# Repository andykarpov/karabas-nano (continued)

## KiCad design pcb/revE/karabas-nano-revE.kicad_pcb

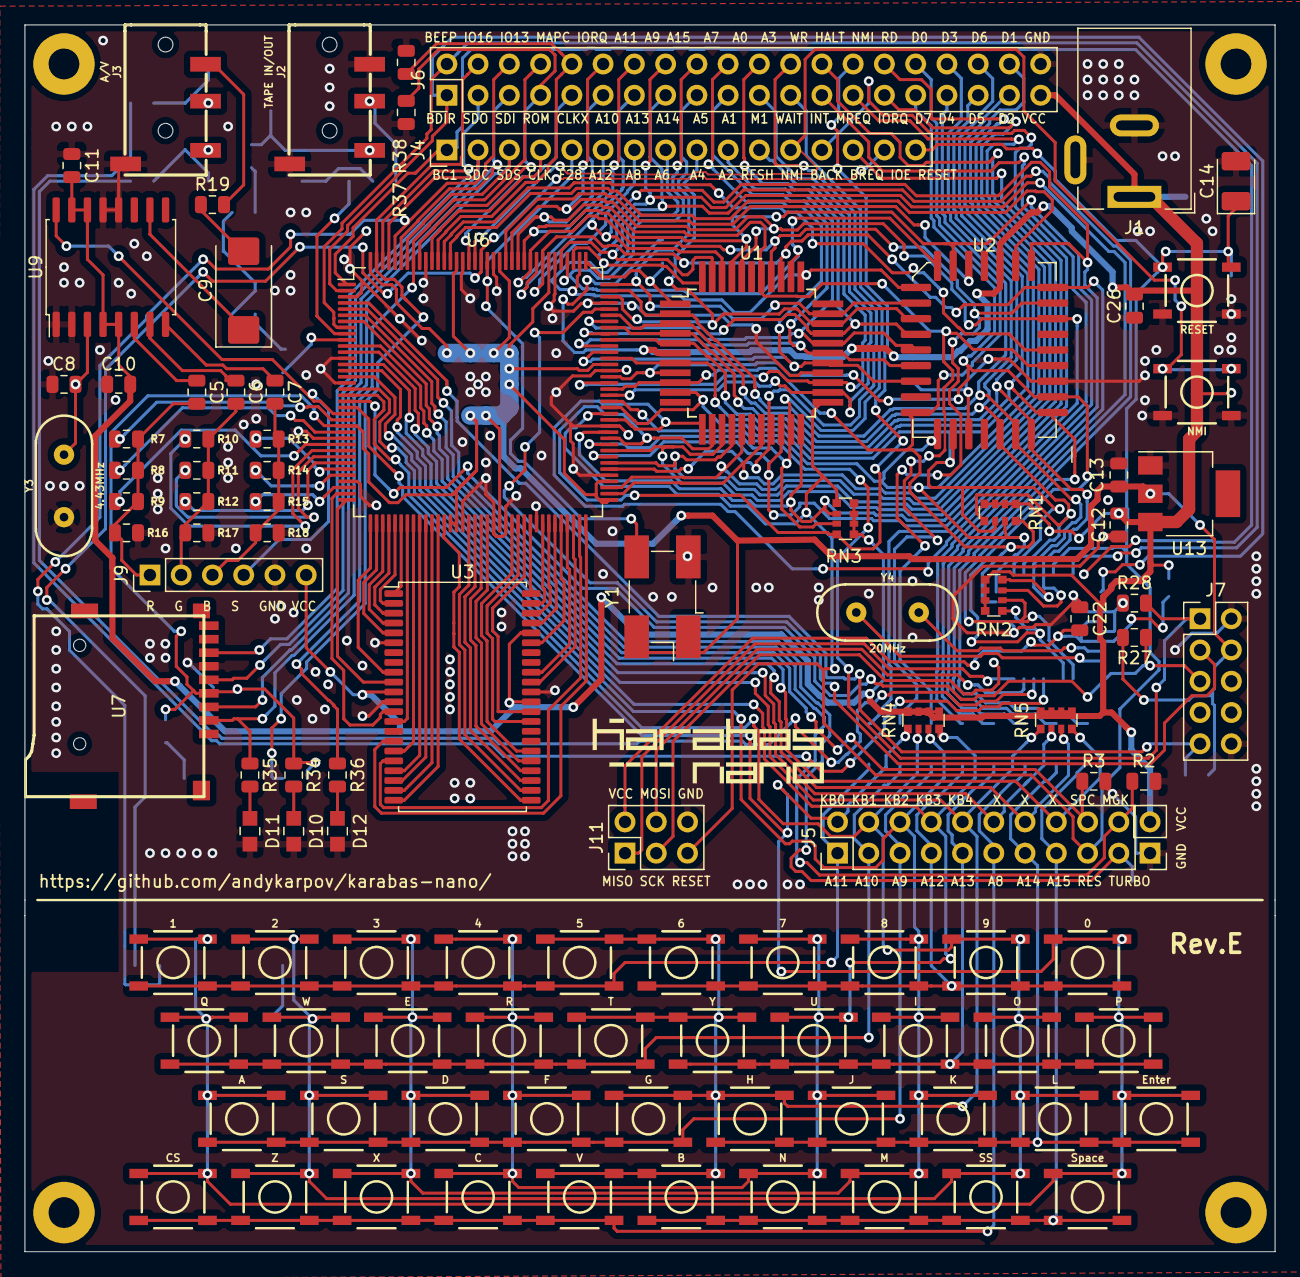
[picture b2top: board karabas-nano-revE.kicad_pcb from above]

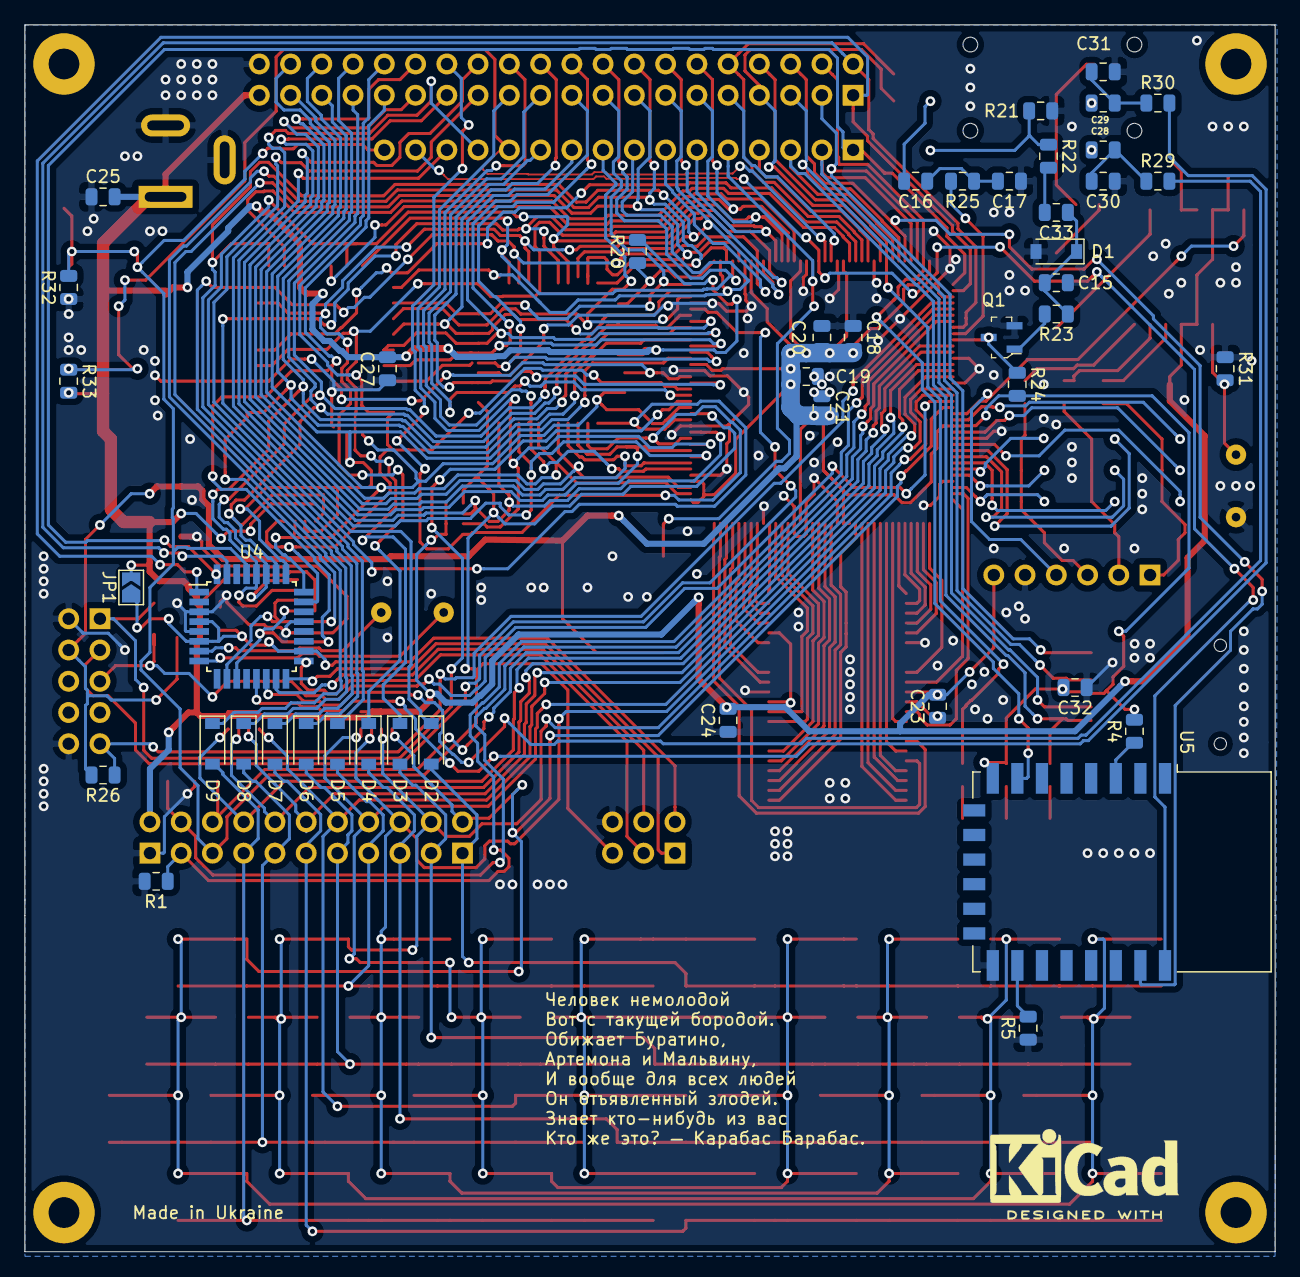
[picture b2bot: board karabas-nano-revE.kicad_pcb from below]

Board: 2 copper layers, 101.6 x 99.7 mm, 153 parts (45 on the bottom side), 160 nets.

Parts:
C5, C6, C7, C16, C18, C19, C20, C21, C22, C23, C24, C25, C26, C27, C32: 100nF; C_0805_2012Metric
C8: 10p; C_0805_2012Metric
C9: 220uF; CP_EIA-7343-31_Kemet-D_Pad2.25x2.55mm_HandSolder
C10, C11, C12, C13, C28, C29: 10uF; C_0805_2012Metric
C14: 10uF; CP_EIA-3528-21_Kemet-B_Pad1.50x2.35mm_HandSolder
C15, C33: 10nF; C_0805_2012Metric
C17: 3n3; C_0805_2012Metric
C30, C31: 1nF; C_0805_2012Metric
D1, D2, D3, D4, D5, D6, D7, D8, D9: 1N4148W; D_SOD-123
D10: PWR; 0805
D11: SD; 0805
D12: MMC; 0805
H1, H2, H3, H4: MountingHole; MountingHole_2.5mm_Pad
J1: DC 5V; BarrelJack_Wuerth_6941xx301002
J2: TAPE IN/OUT; AUDIO_JACK_3.5MM_SMD
J3: A/V; AUDIO_JACK_3.5MM_SMD
J4: BUS; PinHeader_1x16_P2.54mm_Vertical
J5: KEYBOARD; PinHeader_2x10_P2.54mm_Vertical
J6: BUS; PinHeader_2x20_P2.54mm_Vertical
J7: JTAG; PinHeader_2x05_P2.54mm_Vertical
J9: RGB; PinHeader_1x06_P2.54mm_Vertical
J10: PWR; PinHeader_1x02_P2.54mm_Vertical
J11: AVR ISP; PinHeader_2x03_P2.54mm_Vertical
JP1: SolderJumper_2_Open; SolderJumper-2_P1.3mm_Open_TrianglePad1.0x1.5mm
Q1: BC846B; SOT-23-3
R1, R2, R3, R4, R5, R21, R23, R24, R26, R27, R28, R29, R30, R33, R37, R38: 10k; R_0805_2012Metric
R7, R10, R13, R22: 510; R_0805_2012Metric
R8, R11, R14: 1k; R_0805_2012Metric
R9, R12, R15: 2k; R_0805_2012Metric
R16, R17, R18, R19: 75; R_0805_2012Metric
R20: 2k2; R_0805_2012Metric
R25: 33k; R_0805_2012Metric
R31: 4,7M; R_0805_2012Metric
R32: 47k; R_0805_2012Metric
R34, R35, R36: 470; R_0805_2012Metric
RN1, RN2, RN3, RN4, RN5: 10k; R_Array_Convex_4x0612
SW1: RESET; TACTILE_SWITCH_SMD_5.2MM
SW2: NMI; TACTILE_SWITCH_SMD_5.2MM
SW3: 1; TACTILE_SWITCH_SMD_5.2MM
SW4: 2; TACTILE_SWITCH_SMD_5.2MM
SW5: 3; TACTILE_SWITCH_SMD_5.2MM
SW6: 4; TACTILE_SWITCH_SMD_5.2MM
SW7: 5; TACTILE_SWITCH_SMD_5.2MM
SW8: 6; TACTILE_SWITCH_SMD_5.2MM
SW9: 7; TACTILE_SWITCH_SMD_5.2MM
SW10: 8; TACTILE_SWITCH_SMD_5.2MM
SW11: 9; TACTILE_SWITCH_SMD_5.2MM
SW12: 0; TACTILE_SWITCH_SMD_5.2MM
SW13: Q; TACTILE_SWITCH_SMD_5.2MM
SW14: A; TACTILE_SWITCH_SMD_5.2MM
SW15: CS; TACTILE_SWITCH_SMD_5.2MM
SW16: W; TACTILE_SWITCH_SMD_5.2MM
SW17: S; TACTILE_SWITCH_SMD_5.2MM
SW18: Z; TACTILE_SWITCH_SMD_5.2MM
SW19: E; TACTILE_SWITCH_SMD_5.2MM
SW20: D; TACTILE_SWITCH_SMD_5.2MM
SW21: X; TACTILE_SWITCH_SMD_5.2MM
SW22: R; TACTILE_SWITCH_SMD_5.2MM
SW23: F; TACTILE_SWITCH_SMD_5.2MM
SW24: C; TACTILE_SWITCH_SMD_5.2MM
SW25: T; TACTILE_SWITCH_SMD_5.2MM
SW26: G; TACTILE_SWITCH_SMD_5.2MM
SW27: V; TACTILE_SWITCH_SMD_5.2MM
SW28: Y; TACTILE_SWITCH_SMD_5.2MM
SW29: H; TACTILE_SWITCH_SMD_5.2MM
SW30: B; TACTILE_SWITCH_SMD_5.2MM
SW31: U; TACTILE_SWITCH_SMD_5.2MM
SW32: J; TACTILE_SWITCH_SMD_5.2MM
SW33: N; TACTILE_SWITCH_SMD_5.2MM
SW34: I; TACTILE_SWITCH_SMD_5.2MM
SW35: K; TACTILE_SWITCH_SMD_5.2MM
SW36: M; TACTILE_SWITCH_SMD_5.2MM
SW37: O; TACTILE_SWITCH_SMD_5.2MM
SW38: L; TACTILE_SWITCH_SMD_5.2MM
SW39: SS; TACTILE_SWITCH_SMD_5.2MM
SW40: P; TACTILE_SWITCH_SMD_5.2MM
SW41: Enter; TACTILE_SWITCH_SMD_5.2MM
SW42: Space; TACTILE_SWITCH_SMD_5.2MM
U1: Z80; TQFP-44_14x14mm_P0.8mm
U2: 27C512; PLCC-32_11.4x14.0mm_P1.27mm-bigpads
U3: BS62LV1600; TSOP-II-44_10.16x18.41mm_P0.8mm
U4: ATmega8A-AU; TQFP-32_7x7mm_P0.8mm
U5: ESP-12E
U6: EPM3256ATC144; LQFP-144_20x20mm_P0.5mm
U7: MicroSD; GCT-MEM2055-00-190-01-A
U9: AD724; SOIC-16W_7.5x10.3mm_P1.27mm
U13: LM1117-3.3; SOT-223
Y1: 28MHz; Oscillator_SMD_EuroQuartz_XO91-4Pin_7.0x5.0mm_HandSoldering
Y3: 4.43MHz; HC49US
Y4: 20MHz; HC49US

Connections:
+3V3: C13.2, C18.2, C19.2, C20.2, C21.2, C32.2, J7.4, R4.2, R24.2, R26.2, R27.2, R34.1, U5.8, U6.24, U6.50, U6.51, U6.58, U6.73, U6.76, U6.95, U6.115, U6.123, U6.130, U6.144, U7.4, U13.2, Y1.1, Y1.4
/A0: J6.20, U1.27, U2.11, U6.97
/A1: J6.19, U1.28, U2.10, U6.98
/A2: J4.10, U1.29, U2.9, U6.100
/A3: J6.22, U1.30, U2.8, U6.102
/A4: J4.9, U1.31, U2.7, U6.106
/A5: J6.17, U1.32, U2.6, U6.108
/A6: J4.8, U1.34, U2.5, U6.110
/A7: J6.18, U1.35, U2.4, U6.112
/A8: D7.1, J4.7, U1.36, U2.29, U6.116
/A9: D4.1, J6.14, U1.37, U2.28, U6.118
/A10: D3.1, J6.11, U1.38, U2.24, U6.120
/A11: D2.1, J6.12, U1.40, U2.27, U6.121
/A12: D5.1, J4.6, U1.41, U2.3, U6.119
/A13: D6.1, J6.13, U1.42, U2.30, U6.117
/A14: D8.1, J6.15, U1.43, U6.113
/A15: D9.1, J6.16, U1.44, U6.111
/AVR_MISO: J11.1, U4.16
/AVR_MOSI: J11.4, U4.15
/AVR_SCK: J11.3, U4.17
/AY_BC1: J4.1, U4.32, U6.1
/AY_BDIR: J6.1, U4.1, U6.2
/AY_OUT_L: R30.2, U4.13
/AY_OUT_R: R29.2, U4.14
/B0: R15.1, U6.34
/B1: R14.1, U6.32
/B2: R13.1, U6.31
/BEEPER: J6.2, U4.31, U6.8
/BLUE: C7.2, J9.3, R13.2, R14.2, R15.2, R18.1
/CLK28: J4.5, U6.125, Y1.3
/CLKX: J6.9, U6.128
/CLK_BUS: J4.4, U6.134
/CLK_CPU: R20.1, U1.1, U6.109
/CSYNC: J9.4, U6.22, U9.16
/D0: J6.32, RN1.4, U1.9, U2.13, U4.23, U6.91
/D1: J6.38, RN1.3, U1.10, U2.14, U4.24, U6.88
/D2: J6.37, RN1.2, U1.7, U2.15, U4.25, U6.96
/D3: J6.34, RN1.1, U1.3, U2.18, U4.26, U6.103
/D4: J6.33, RN2.4, U1.2, U2.19, U4.27, U6.107
/D5: J6.35, RN2.3, U1.4, U2.20, U4.28, U6.101
/D6: J6.36, RN2.2, U1.5, U2.21, U4.10, U6.99
/D7: J6.31, RN2.1, U1.8, U2.22, U4.11, U6.93
/G0: R12.1, U6.30
/G1: R11.1, U6.29
/G2: R10.1, U6.28
/GREEN: C6.2, J9.2, R10.2, R11.2, R12.2, R17.1
/IO13: J6.6, U5.21, U6.140
/IO16: J6.4, U5.7, U6.143
/IOE: J4.15, U5.22, U6.126
/KA8: D7.2, J5.11, SW15.1, SW15.2, SW18.1, SW18.2, SW21.1, SW21.2, SW24.1, SW24.2, SW27.1, SW27.2
/KA9: D4.2, J5.5, SW14.1, SW14.2, SW17.1, SW17.2, SW20.1, SW20.2, SW23.1, SW23.2, SW26.1, SW26.2
/KA10: D3.2, J5.3, SW13.1, SW13.2, SW16.1, SW16.2, SW19.1, SW19.2, SW22.1, SW22.2, SW25.1, SW25.2
/KA11: D2.2, J5.1, SW3.1, SW3.2, SW4.1, SW4.2, SW5.1, SW5.2, SW6.1, SW6.2, SW7.1, SW7.2
/KA12: D5.2, J5.7, SW8.1, SW8.2, SW9.1, SW9.2, SW10.1, SW10.2, SW11.1, SW11.2, SW12.1, SW12.2
/KA13: D6.2, J5.9, SW28.1, SW28.2, SW31.1, SW31.2, SW34.1, SW34.2, SW37.1, SW37.2, SW40.1, SW40.2
/KA14: D8.2, J5.13, SW29.1, SW29.2, SW32.1, SW32.2, SW35.1, SW35.2, SW38.1, SW38.2, SW41.1, SW41.2
/KA15: D9.2, J5.15, SW30.1, SW30.2, SW33.1, SW33.2, SW36.1, SW36.2, SW39.1, SW39.2, SW42.1, SW42.2
/KB0: J5.2, RN4.1, SW3.3, SW3.4, SW12.3, SW12.4, SW13.3, SW13.4, SW14.3, SW14.4, SW15.3, SW15.4, SW40.3, SW40.4, SW41.3, SW41.4, SW42.3, SW42.4, U6.21
/KB1: J5.4, RN4.2, SW4.3, SW4.4, SW11.3, SW11.4, SW16.3, SW16.4, SW17.3, SW17.4, SW18.3, SW18.4, SW37.3, SW37.4, SW38.3, SW38.4, SW39.3, SW39.4, U6.19
/KB2: J5.6, RN4.3, SW5.3, SW5.4, SW10.3, SW10.4, SW19.3, SW19.4, SW20.3, SW20.4, SW21.3, SW21.4, SW34.3, SW34.4, SW35.3, SW35.4, SW36.3, SW36.4, U6.18
/KB3: J5.8, RN4.4, SW6.3, SW6.4, SW9.3, SW9.4, SW22.3, SW22.4, SW23.3, SW23.4, SW24.3, SW24.4, SW31.3, SW31.4, SW32.3, SW32.4, SW33.3, SW33.4, U6.16
/KB4: J5.10, RN5.1, SW7.3, SW7.4, SW8.3, SW8.4, SW25.3, SW25.4, SW26.3, SW26.4, SW27.3, SW27.4, SW28.3, SW28.4, SW29.3, SW29.4, SW30.3, SW30.4, U6.15
/KB5: J5.12, RN5.2, U6.14
/KB6: J5.14, RN5.3, U6.12
/KB7: J5.16, RN5.4, U6.11
/MA0: U3.5, U6.38
/MA1: U3.4, U6.39
/MA2: U3.3, U6.40
/MA3: U3.2, U6.41
/MA4: U3.1, U6.42
/MA5: U3.44, U6.63
/MA6: U3.43, U6.65
/MA7: U3.42, U6.66
/MA8: U3.39, U6.68
/MA9: U3.28, U6.60
/MA10: U3.27, U6.56
/MA11: U3.26, U6.55
/MA12: U3.25, U6.54
/MA13: U3.24, U6.53
/MA14: U3.23, U6.49
/MA15: U3.22, U6.48
/MA16: U3.21, U6.47
/MA17: U3.20, U6.46
/MA18: U3.19, U6.45
/MA19: U3.18, U6.71
/MA20: U3.16, U6.72
/MAGIC: J5.20, R2.1, U6.6
/MAPCOND: J6.8, R36.1, U6.137
/MD0: U3.9, U6.37
/MD1: U3.10, U6.36
/MD2: U3.13, U6.35
/MD3: U3.14, U6.43
/MD4: U3.31, U6.61
/MD5: U3.32, U6.62
/MD6: U3.35, U6.70
/MD7: U3.36, U6.69
/R0: R9.1, U6.27
/R1: R8.1, U6.25
/R2: R7.1, U6.23
/RED: C5.2, J9.1, R7.2, R8.2, R9.2, R16.1
/ROM_A14: U2.31, U6.131
/ROM_A15: U2.2, U6.122
/SD_CLK: J4.2, U6.141, U7.5
/SD_DI: J6.5, U6.139, U7.3
/SD_DO: J6.3, U6.142, U7.7
/SPECIAL: J5.18, R3.1, U6.7
/TCK: J7.1, R28.2, U6.89
/TDI: J7.9, R26.1, U6.4
/TDO: J7.3, U6.104
/TMS: J7.5, R27.1, U6.20
/TURBO: J5.19, R1.1, U6.5
/VCCJP: C22.2, J11.2, JP1.1, U4.4, U4.6, U4.18
/~BTN_NMI: J4.12, R33.1, SW2.1, SW2.2, U6.127
/~BUSACK: J4.13, U1.20, U6.80
/~BUSREQ: J4.14, RN3.2, U1.22, U6.84
/~BUS_IORQGE: J6.10, R38.1, U6.133
/~BUS_ROMCS: J6.7, R37.1, U6.136
/~HALT: J6.26, U1.14, U6.81
/~INT: J6.25, U1.12, U6.86
/~IORQ: J6.29, U1.16, U6.75
/~M1: J6.21, U1.24, U6.90
/~MRD: U3.41, U6.67
/~MREQ: J6.27, U1.15, U6.79
/~MWR: U3.17, U6.44
/~NMI: J6.28, RN3.4, U1.13, U6.83
/~RD: J6.30, U1.18, U6.74
/~RFSH: J4.11, U1.25, U6.92
/~ROMCS: U2.25, U6.132
/~SD_CS: J4.3, R35.1, U6.138, U7.2
/~WAIT: J6.23, RN3.3, U1.21, U6.82
/~WR: J6.24, U1.19, U6.78
GND: C8.1, C10.1, C11.1, C12.1, C13.1, C14.2, C15.1, C17.1, C18.1, C19.1, C20.1, C21.1, C22.1, C23.1, C24.1, C25.1, C26.1, C27.1, C30.1, C31.1, C32.1, D1.2, D10.2, D11.2, D12.2, J1.2, J1.3, J2.1, J2.2, J3.1, J6.40, J7.2, J7.10, J9.5, J10.1, J11.6, Q1.2, R1.2, R2.2, R3.2, R5.1, R16.2, R17.2, R18.2, R21.1, R28.1, R31.1, R32.1, R37.2, R38.2, SW1.3, SW1.4, SW2.3, SW2.4, U1.26, U2.16, U2.23, U3.6, U3.12, U3.34, U4.3, U4.5, U4.21, U5.15, U6.3, U6.13, U6.17, U6.26, U6.33, U6.52, U6.57, U6.59, U6.64, U6.77, U6.85, U6.94, U6.105, U6.114, U6.124, U6.129, U6.135, U7.6, U9.1, U9.2, U9.12, U9.13, U13.1, Y1.2, Y3.1
unnamed: C5.1, U9.6
unnamed: C6.1, U9.7
unnamed: C7.1, U9.8
unnamed: C8.2, R31.2, U9.3, Y3.2
unnamed: C9.1, U9.10
unnamed: C9.2, R19.1
unnamed: C15.2, C33.1, D1.1, R23.1
unnamed: C16.1, C17.2, R25.1
unnamed: C16.2, J2.3
unnamed: C28.1, C30.2, R29.1
unnamed: C28.2, J3.4
unnamed: C29.1, C31.2, R30.1
unnamed: C29.2, J3.3
unnamed: C33.2, R22.2
unnamed: D10.1, R34.2
unnamed: D11.1, R35.2
unnamed: D12.1, R36.2
unnamed: J2.4, R21.2, R22.1
unnamed: J3.2, R19.2
unnamed: Q1.1, R23.2
unnamed: R4.1, U5.3
unnamed: R5.2, U5.16
unnamed: U4.7, Y4.2
unnamed: U4.8, Y4.1
TAPE_IN: Q1.3, R24.1, U6.10
TAPE_OUT: R25.2, U6.9
VCC: C10.2, C11.2, C12.2, C23.2, C24.2, C25.2, C26.2, C27.2, J1.1, J6.39, J9.6, J10.2, JP1.2, R20.2, R33.2, RN1.5, RN1.6, RN1.7, RN1.8, RN2.5, RN2.6, RN2.7, RN2.8, RN3.5, RN3.6, RN3.7, RN3.8, RN4.5, RN4.6, RN4.7, RN4.8, RN5.5, RN5.6, RN5.7, RN5.8, U1.6, U2.32, U3.11, U3.33, U3.40, U9.4, U9.5, U9.14, U9.15, U13.3
~RESET: C14.1, J4.16, J5.17, J11.5, R32.2, RN3.1, SW1.1, SW1.2, U1.23, U4.29, U6.87

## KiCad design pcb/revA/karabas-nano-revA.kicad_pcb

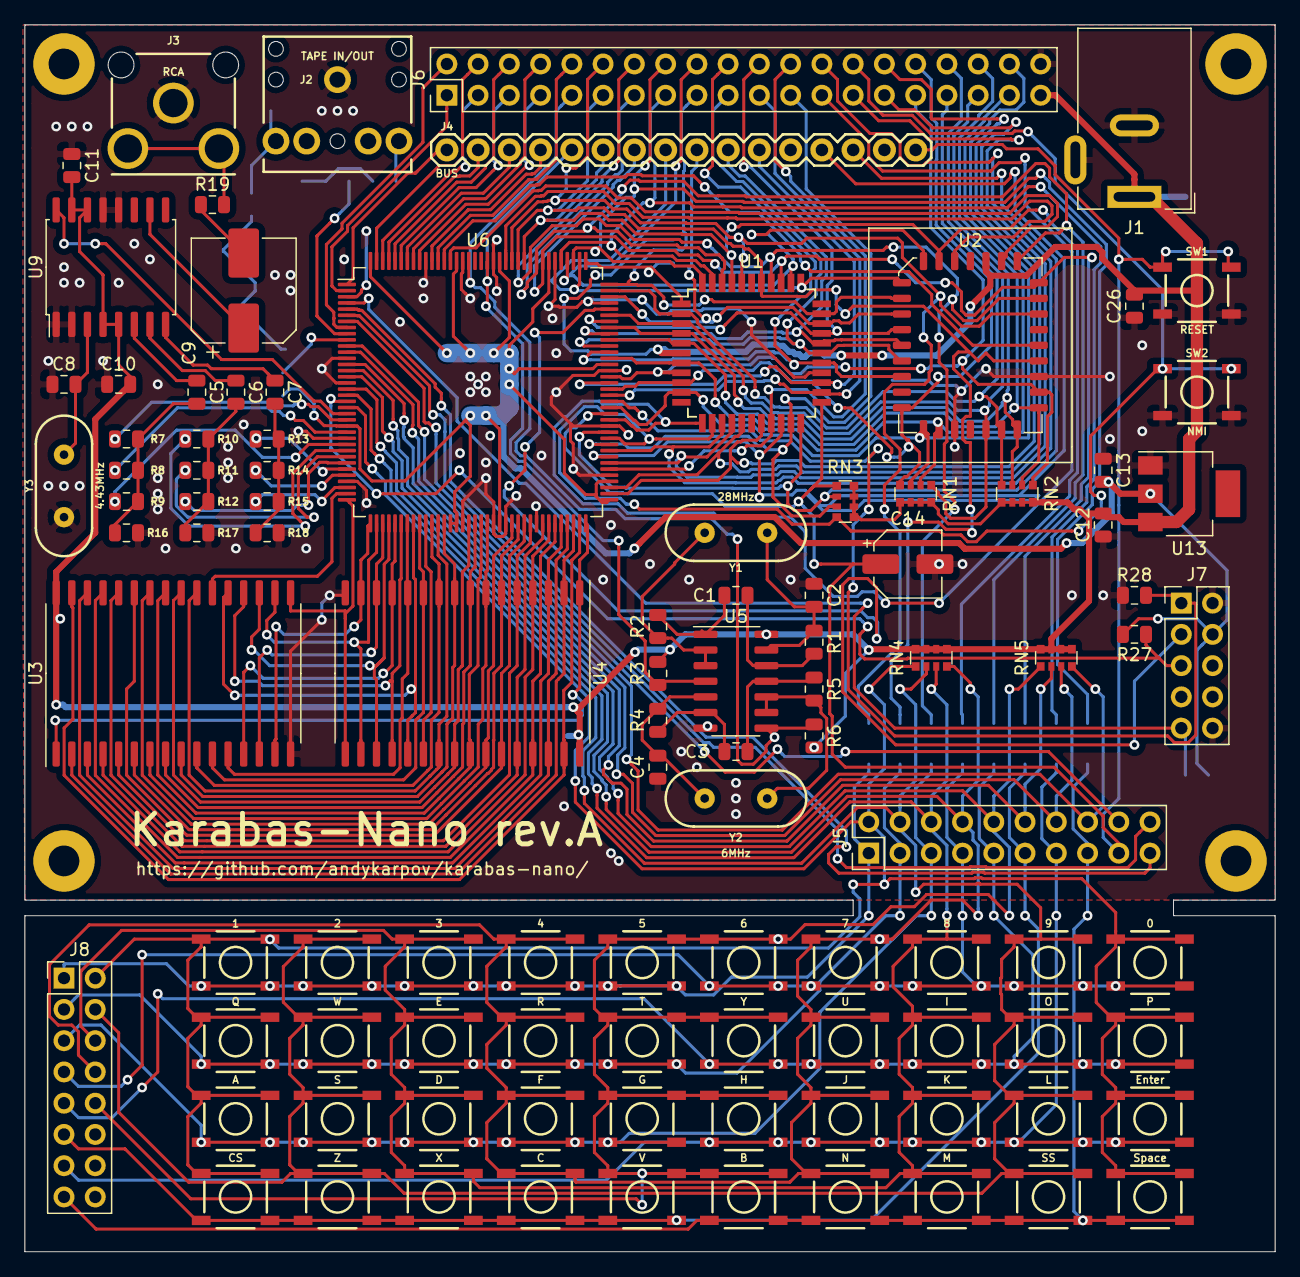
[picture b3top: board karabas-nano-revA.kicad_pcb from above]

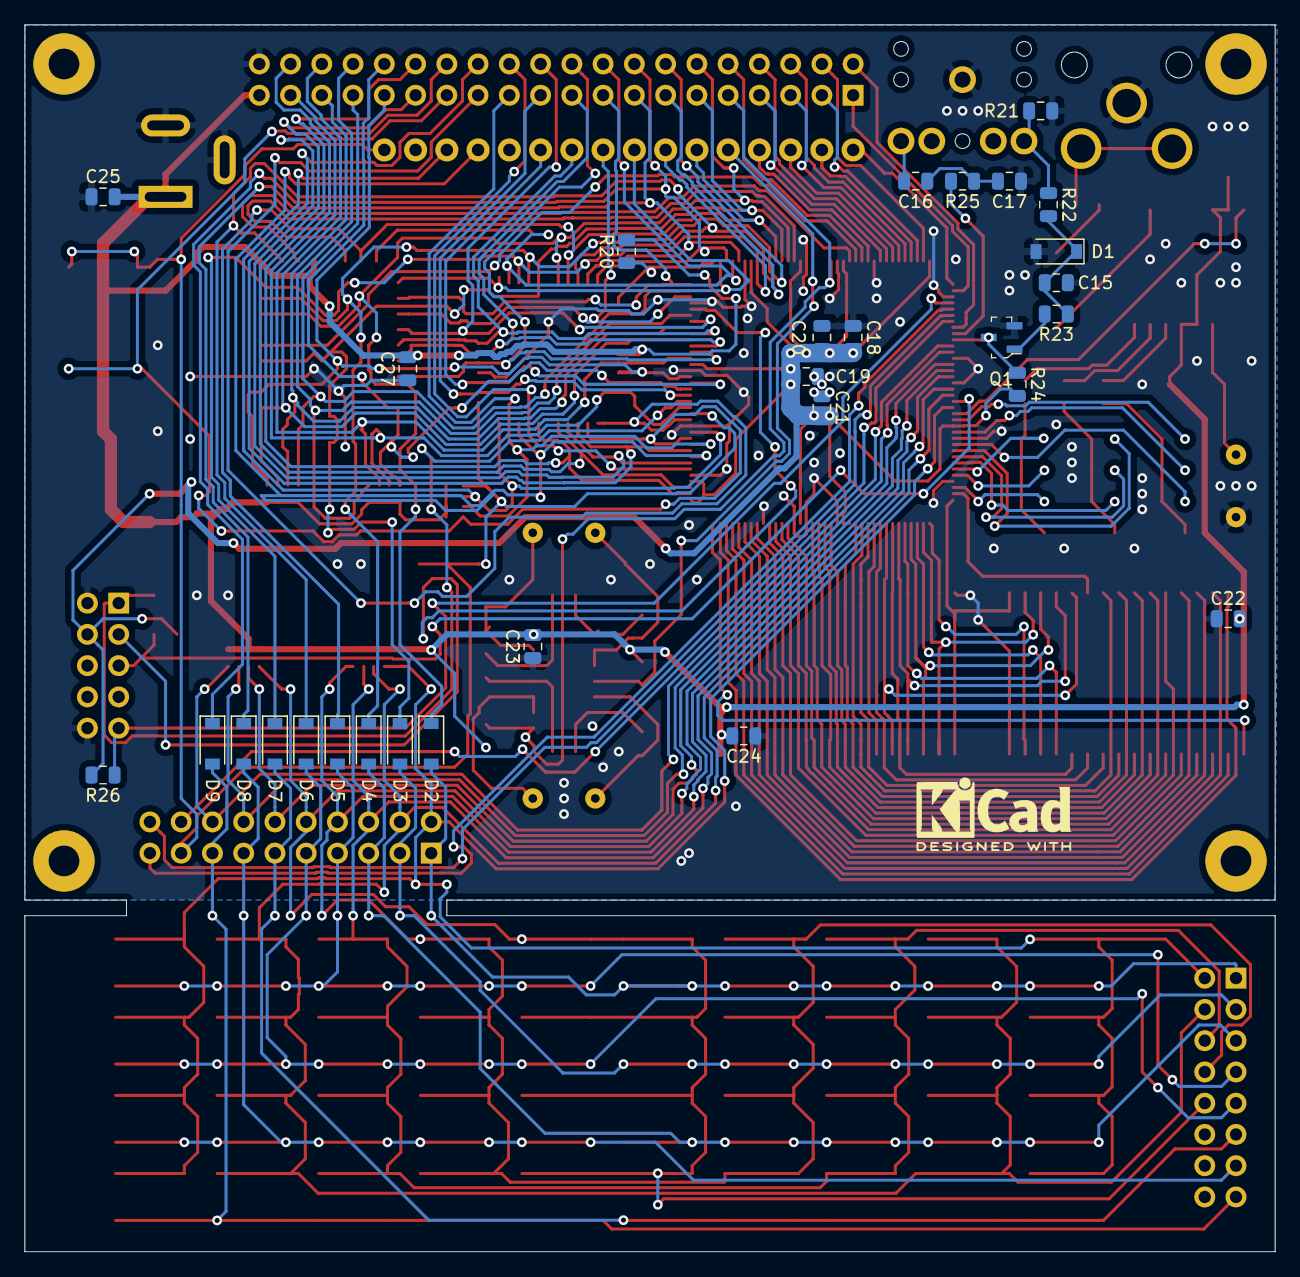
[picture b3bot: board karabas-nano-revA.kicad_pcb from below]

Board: 2 copper layers, 101.6 x 99.7 mm, 135 parts (29 on the bottom side), 148 nets.

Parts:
C1, C3: 100p; C_0805_2012Metric
C2, C4: 22p; C_0805_2012Metric
C5, C6, C7, C16, C18, C19, C20, C21, C22, C23, C24, C25, C26, C27: 100nF; C_0805_2012Metric
C8: 10p; C_0805_2012Metric
C9: 220uF; CP_Elec_8x6.5
C10, C11, C12, C13: 10uF; C_0805_2012Metric
C14: 10uF; CP_Elec_5x4.4
C15: 10nF; C_0805_2012Metric
C17: 3n3; C_0805_2012Metric
D1, D2, D3, D4, D5, D6, D7, D8, D9: 1N4148W; D_SOD-123
H1, H2, H3, H4: MountingHole; MountingHole_2.5mm_Pad
J1: DC 5V; BarrelJack_Wuerth_6941xx301002
J2: TAPE IN/OUT; AUDIO-JACK
J3: RCA
J4: BUS; 1X16
J5: KEYBOARD; PinHeader_2x10_P2.54mm_Vertical
J6: BUS; PinHeader_2x20_P2.54mm_Vertical
J7: JTAG; PinHeader_2x05_P2.54mm_Vertical
J8: KEYBOARD; PinHeader_2x08_P2.54mm_Vertical
K0: 0; TACTILE_SWITCH_SMD_5.2MM
K1: 1; TACTILE_SWITCH_SMD_5.2MM
K2: 2; TACTILE_SWITCH_SMD_5.2MM
K3: 3; TACTILE_SWITCH_SMD_5.2MM
K4: 4; TACTILE_SWITCH_SMD_5.2MM
K5: 5; TACTILE_SWITCH_SMD_5.2MM
K6: 6; TACTILE_SWITCH_SMD_5.2MM
K7: 7; TACTILE_SWITCH_SMD_5.2MM
K8: 8; TACTILE_SWITCH_SMD_5.2MM
K9: 9; TACTILE_SWITCH_SMD_5.2MM
KA1: A; TACTILE_SWITCH_SMD_5.2MM
KB1: B; TACTILE_SWITCH_SMD_5.2MM
KC1: C; TACTILE_SWITCH_SMD_5.2MM
KCS1: CS; TACTILE_SWITCH_SMD_5.2MM
KD1: D; TACTILE_SWITCH_SMD_5.2MM
KE1: E; TACTILE_SWITCH_SMD_5.2MM
KEnter1: Enter; TACTILE_SWITCH_SMD_5.2MM
KF1: F; TACTILE_SWITCH_SMD_5.2MM
KG1: G; TACTILE_SWITCH_SMD_5.2MM
KH1: H; TACTILE_SWITCH_SMD_5.2MM
KI1: I; TACTILE_SWITCH_SMD_5.2MM
KJ1: J; TACTILE_SWITCH_SMD_5.2MM
KK1: K; TACTILE_SWITCH_SMD_5.2MM
KL1: L; TACTILE_SWITCH_SMD_5.2MM
KM1: M; TACTILE_SWITCH_SMD_5.2MM
KN1: N; TACTILE_SWITCH_SMD_5.2MM
KO1: O; TACTILE_SWITCH_SMD_5.2MM
KP1: P; TACTILE_SWITCH_SMD_5.2MM
KQ1: Q; TACTILE_SWITCH_SMD_5.2MM
KR1: R; TACTILE_SWITCH_SMD_5.2MM
KS1: S; TACTILE_SWITCH_SMD_5.2MM
KSS1: SS; TACTILE_SWITCH_SMD_5.2MM
KSpace1: Space; TACTILE_SWITCH_SMD_5.2MM
KT1: T; TACTILE_SWITCH_SMD_5.2MM
KU1: U; TACTILE_SWITCH_SMD_5.2MM
KV1: V; TACTILE_SWITCH_SMD_5.2MM
KW1: W; TACTILE_SWITCH_SMD_5.2MM
KX1: X; TACTILE_SWITCH_SMD_5.2MM
KY1: Y; TACTILE_SWITCH_SMD_5.2MM
KZ1: Z; TACTILE_SWITCH_SMD_5.2MM
Q1: BC846B; SOT-23-3
R1, R2, R4, R5: 470; R_0805_2012Metric
R3, R6: 4k7; R_0805_2012Metric
R7, R10, R13, R22: 510; R_0805_2012Metric
R8, R11, R14: 1k; R_0805_2012Metric
R9, R12, R15: 2k; R_0805_2012Metric
R16, R17, R18, R19: 75; R_0805_2012Metric
R20: 2k2; R_0805_2012Metric
R21, R23, R24, R26, R27, R28: 10k; R_0805_2012Metric
R25: 33k; R_0805_2012Metric
RN1, RN2, RN3, RN4, RN5: 10k; R_Array_Convex_4x0612
SW1: RESET; TACTILE_SWITCH_SMD_5.2MM
SW2: NMI; TACTILE_SWITCH_SMD_5.2MM
U1: Z80; TQFP-44_10x10mm_P0.8mm
U2: 27C512; PLCC-32_11.4x14.0mm_P1.27mm
U3, U4: BS62LV4006; SSOP-32_11.305x20.495mm_P1.27mm
U5: 74HC04; SOIC-14_3.9x8.7mm_P1.27mm
U6: EPM3256ATC144; LQFP-144_20x20mm_P0.5mm
U9: AD724; SOIC-16W_7.5x10.3mm_P1.27mm
U13: LM1117-3.3; SOT-223
Y1: 28MHz; HC49US
Y2: 6MHz; HC49US
Y3: 4.43MHz; HC49US

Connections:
+3V3: C13.2, C18.2, C19.2, C20.2, C21.2, J7.4, R24.2, R26.2, R27.2, U6.24, U6.50, U6.51, U6.58, U6.73, U6.76, U6.95, U6.115, U6.123, U6.130, U6.144, U13.2
/A0: J6.20, U1.27, U2.11, U6.97
/A1: J6.19, U1.28, U2.10, U6.98
/A2: J4.10, U1.29, U2.9, U6.100
/A3: J6.22, U1.30, U2.8, U6.102
/A4: J4.9, U1.31, U2.7, U6.106
/A5: J6.17, U1.32, U2.6, U6.108
/A6: J4.8, U1.34, U2.5, U6.110
/A7: J6.18, U1.35, U2.4, U6.112
/A8: D7.1, J4.7, U1.36, U2.29, U6.116
/A9: D4.1, J6.14, U1.37, U2.28, U6.118
/A10: D3.1, J6.11, U1.38, U2.24, U6.120
/A11: D2.1, J6.12, U1.40, U2.27, U6.121
/A12: D5.1, J4.6, U1.41, U2.3, U6.119
/A13: D6.1, J6.13, U1.42, U2.30, U6.117
/A14: D8.1, J6.15, U1.43, U6.113
/A15: D9.1, J6.16, U1.44, U6.111
/B0: R15.1, U6.34
/B1: R14.1, U6.32
/B2: R13.1, U6.31
/BEEPER: J6.2, U6.8
/CLK28: J4.5, R3.1, U5.4, U6.125
/CLKX: J6.9, R6.1, U5.8, U6.128
/CLK_BUS: J4.4, U6.134
/CLK_CPU: R20.1, U1.1, U6.109
/CSYNC: U6.22, U9.16
/D0: J6.32, RN1.4, U1.9, U2.13, U6.91
/D1: J6.38, RN1.3, U1.10, U2.14, U6.88
/D2: J6.37, RN1.2, U1.7, U2.15, U6.96
/D3: J6.34, RN1.1, U1.3, U2.18, U6.103
/D4: J6.33, RN2.4, U1.2, U2.19, U6.107
/D5: J6.35, RN2.3, U1.4, U2.20, U6.101
/D6: J6.36, RN2.2, U1.5, U2.21, U6.99
/D7: J6.31, RN2.1, U1.8, U2.22, U6.93
/G0: R12.1, U6.30
/G1: R11.1, U6.29
/G2: R10.1, U6.28
/IO10: J6.8, U6.137
/IO11: J4.3, U6.138
/IO12: J6.5, U6.139
/IO13: J6.6, U6.140
/IO14: J4.2, U6.141
/IO15: J6.3, U6.142
/IO16: J6.4, U6.143
/IO18: J4.1, U6.1
/IO19: J6.1, U6.2
/KA8: D7.2, J5.11, J8.11, KC1.1, KC1.2, KCS1.1, KCS1.2, KV1.1, KV1.2, KX1.1, KX1.2, KZ1.1, KZ1.2
/KA9: D4.2, J5.5, J8.5, KA1.1, KA1.2, KD1.1, KD1.2, KF1.1, KF1.2, KG1.1, KG1.2, KS1.1, KS1.2
/KA10: D3.2, J5.3, J8.3, KE1.1, KE1.2, KQ1.1, KQ1.2, KR1.1, KR1.2, KT1.1, KT1.2, KW1.1, KW1.2
/KA11: D2.2, J5.1, J8.1, K1.1, K1.2, K2.1, K2.2, K3.1, K3.2, K4.1, K4.2, K5.1, K5.2
/KA12: D5.2, J5.7, J8.7, K0.1, K0.2, K6.1, K6.2, K7.1, K7.2, K8.1, K8.2, K9.1, K9.2
/KA13: D6.2, J5.9, J8.9, KI1.1, KI1.2, KO1.1, KO1.2, KP1.1, KP1.2, KU1.1, KU1.2, KY1.1, KY1.2
/KA14: D8.2, J5.13, J8.13, KEnter1.1, KEnter1.2, KH1.1, KH1.2, KJ1.1, KJ1.2, KK1.1, KK1.2, KL1.1, KL1.2
/KA15: D9.2, J5.15, J8.15, KB1.1, KB1.2, KM1.1, KM1.2, KN1.1, KN1.2, KSS1.1, KSS1.2, KSpace1.1, KSpace1.2
/KB0: J5.2, J8.2, K0.3, K0.4, K1.3, K1.4, KA1.3, KA1.4, KCS1.3, KCS1.4, KEnter1.3, KEnter1.4, KP1.3, KP1.4, KQ1.3, KQ1.4, KSpace1.3, KSpace1.4, RN4.1, U6.21
/KB1: J5.4, J8.4, K2.3, K2.4, K9.3, K9.4, KL1.3, KL1.4, KO1.3, KO1.4, KS1.3, KS1.4, KSS1.3, KSS1.4, KW1.3, KW1.4, KZ1.3, KZ1.4, RN4.2, U6.19
/KB2: J5.6, J8.6, K3.3, K3.4, K8.3, K8.4, KD1.3, KD1.4, KE1.3, KE1.4, KI1.3, KI1.4, KK1.3, KK1.4, KM1.3, KM1.4, KX1.3, KX1.4, RN4.3, U6.18
/KB3: J5.8, J8.8, K4.3, K4.4, K7.3, K7.4, KC1.3, KC1.4, KF1.3, KF1.4, KJ1.3, KJ1.4, KN1.3, KN1.4, KR1.3, KR1.4, KU1.3, KU1.4, RN4.4, U6.16
/KB4: J5.10, J8.10, K5.3, K5.4, K6.3, K6.4, KB1.3, KB1.4, KG1.3, KG1.4, KH1.3, KH1.4, KT1.3, KT1.4, KV1.3, KV1.4, KY1.3, KY1.4, RN5.1, U6.15
/KB5: J5.12, RN5.2, U6.14
/KB6: J5.14, RN5.3, U6.12
/KB7: J5.16, RN5.4, U6.11
/MA0: U3.12, U4.12, U6.43
/MA1: U3.11, U4.11, U6.45
/MA2: U3.10, U4.10, U6.47
/MA3: U3.9, U4.9, U6.49
/MA4: U3.8, U4.8, U6.54
/MA5: U3.7, U4.7, U6.56
/MA6: U3.6, U4.6, U6.61
/MA7: U3.5, U4.5, U6.63
/MA8: U3.27, U4.27, U6.62
/MA9: U3.26, U4.26, U6.60
/MA10: U3.23, U4.23, U6.48
/MA11: U3.25, U4.25, U6.55
/MA12: U3.4, U4.4, U6.66
/MA13: U3.28, U4.28, U6.65
/MA14: U3.3, U4.3, U6.68
/MA15: U3.31, U4.31, U6.71
/MA16: U3.2, U4.2, U6.70
/MA17: U3.30, U4.30, U6.69
/MA18: U3.1, U4.1, U6.72
/MAGIC: J5.20, U6.6
/MD0: U3.13, U4.13, U6.41
/MD1: U3.14, U4.14, U6.39
/MD2: U3.15, U4.15, U6.37
/MD3: U3.17, U4.17, U6.36
/MD4: U3.18, U4.18, U6.38
/MD5: U3.19, U4.19, U6.40
/MD6: U3.20, U4.20, U6.42
/MD7: U3.21, U4.21, U6.44
/R0: R9.1, U6.27
/R1: R8.1, U6.25
/R2: R7.1, U6.23
/ROM_A14: U2.31, U6.131
/ROM_A15: U2.2, U6.122
/SPECIAL: J5.18, U6.7
/TCK: J7.1, R28.2, U6.89
/TDI: J7.9, R26.1, U6.4
/TDO: J7.3, U6.104
/TMS: J7.5, R27.1, U6.20
/TURBO: J5.19, U6.5
/~BUSACK: J4.13, U1.20, U6.80
/~BUSREQ: J4.14, RN3.2, U1.22, U6.84
/~BUS_IORQGE: J6.10, U6.133
/~BUS_ROMCS: J6.7, U6.136
/~HALT: J6.26, U1.14, U6.81
/~INT: J6.25, U1.12, U6.86
/~IORQ: J6.29, U1.16, U6.75
/~M1: J6.21, U1.24, U6.90
/~MCS0: U3.22, U6.35
/~MCS1: U4.22, U6.46
/~MRD: U3.24, U4.24, U6.53
/~MREQ: J6.27, U1.15, U6.79
/~MWR: U3.29, U4.29, U6.67
/~NMI: J6.28, RN3.4, SW2.1, SW2.2, U1.13, U6.83
/~RD: J6.30, U1.18, U6.74
/~RFSH: J4.11, U1.25, U6.92
/~ROMCS: U2.25, U6.132
/~WAIT: J6.23, RN3.3, U1.21, U6.82
/~WR: J6.24, U1.19, U6.78
GND: C2.1, C4.1, C8.1, C10.1, C11.1, C12.1, C13.1, C14.2, C15.1, C17.1, C18.1, C19.1, C20.1, C21.1, C22.1, C23.1, C24.1, C25.1, C26.1, C27.1, D1.2, J1.2, J1.3, J2.SLEE, J3.SHEL, J6.40, J7.2, J7.10, Q1.2, R16.2, R17.2, R18.2, R21.1, R28.1, SW1.3, SW1.4, SW2.3, SW2.4, U1.26, U2.16, U2.23, U3.16, U4.16, U5.7, U6.3, U6.13, U6.17, U6.26, U6.33, U6.52, U6.57, U6.59, U6.64, U6.77, U6.85, U6.94, U6.105, U6.114, U6.124, U6.129, U6.135, U9.1, U9.2, U9.12, U9.13, U13.1, Y3.1
unnamed: C1.1, R2.1, U5.1
unnamed: C1.2, R1.2, U5.12
unnamed: C2.2, R1.1, U5.13, Y1.1
unnamed: C3.1, R5.1, U5.11
unnamed: C3.2, R4.2, U5.6
unnamed: C4.2, R4.1, U5.5, Y2.1
unnamed: C5.1, U9.6
unnamed: C5.2, R7.2, R8.2, R9.2, R16.1
unnamed: C6.1, U9.7
unnamed: C6.2, R10.2, R11.2, R12.2, R17.1
unnamed: C7.1, U9.8
unnamed: C7.2, R13.2, R14.2, R15.2, R18.1
unnamed: C8.2, U9.3, Y3.2
unnamed: C9.1, U9.10
unnamed: C9.2, R19.1
unnamed: C15.2, D1.1, R22.2, R23.1
unnamed: C16.1, C17.2, R25.1
unnamed: C16.2, J2.RING
unnamed: J2.TIP, R21.2, R22.1
unnamed: J3.PIN, J3.SWIT, R19.2
unnamed: Q1.1, R23.2
unnamed: R2.2, U5.2, U5.3, Y1.2
unnamed: R5.2, U5.9, U5.10, Y2.2
TAPE_IN: Q1.3, R24.1, U6.10
TAPE_OUT: R25.2, U6.9
VCC: C10.2, C11.2, C12.2, C22.2, C23.2, C24.2, C25.2, C26.2, C27.2, J1.1, J6.39, R3.2, R6.2, R20.2, RN1.5, RN1.6, RN1.7, RN1.8, RN2.5, RN2.6, RN2.7, RN2.8, RN3.5, RN3.6, RN3.7, RN3.8, RN4.5, RN4.6, RN4.7, RN4.8, RN5.5, RN5.6, RN5.7, RN5.8, U1.6, U2.32, U3.32, U4.32, U5.14, U9.4, U9.5, U9.14, U9.15, U13.3
~RESET: C14.1, J4.16, J5.17, RN3.1, SW1.1, SW1.2, U1.23, U6.87

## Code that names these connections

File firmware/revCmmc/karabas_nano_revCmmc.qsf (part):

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set_global_assignment -name SLOW_SLEW_RATE OFF
set_global_assignment -name FORCE_FITTER_TO_AVOID_PERIPHERY_PLACEMENT_WARNINGS OFF

set_location_assignment PIN_1 -to AY_BC1
set_location_assignment PIN_2 -to AY_BDIR
set_location_assignment PIN_5 -to TURBO
set_location_assignment PIN_6 -to MAGIC
set_location_assignment PIN_7 -to SPECIAL
set_location_assignment PIN_8 -to BEEPER
set_location_assignment PIN_9 -to TAPE_OUT
set_location_assignment PIN_10 -to TAPE_IN
set_location_assignment PIN_22 -to VIDEO_CSYNC
set_location_assignment PIN_23 -to VIDEO_R[2]
set_location_assignment PIN_25 -to VIDEO_R[1]
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set_location_assignment PIN_103 -to D[3]
set_location_assignment PIN_106 -to A[4]
set_location_assignment PIN_107 -to D[4]
set_location_assignment PIN_109 -to CLK_CPU
set_location_assignment PIN_110 -to A[6]
set_location_assignment PIN_111 -to A[15]
set_location_assignment PIN_112 -to A[7]
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set_location_assignment PIN_119 -to A[12]
set_location_assignment PIN_120 -to A[10]
set_location_assignment PIN_121 -to A[11]
set_location_assignment PIN_122 -to ROM_A15
set_location_assignment PIN_125 -to CLK28
set_location_assignment PIN_128 -to CLKX
set_location_assignment PIN_131 -to ROM_A14
set_location_assignment PIN_132 -to N_ROMCS
set_location_assignment PIN_133 -to BUS_N_IORQGE
set_location_assignment PIN_134 -to CLK_BUS
set_location_assignment PIN_136 -to BUS_N_ROMCS
set_location_assignment PIN_138 -to SD_N_CS
set_location_assignment PIN_139 -to SD_DI
set_location_assignment PIN_141 -to SD_CLK
set_location_assignment PIN_142 -to SD_DO



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set_global_assignment -name VHDL_FILE divmmc.vhd
set_global_assignment -name VHDL_FILE karabas_nano_revCmmc.vhd

set_location_assignment PIN_127 -to BTN_NMI
set_location_assignment PIN_126 -to IOE
set_location_assignment PIN_137 -to MAPCOND
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
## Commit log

2019-07-14 initial revision
2019-07-14 revB cpld firmware prototype
2019-07-14 small fixes
2019-07-27 rev.A initial firmware
2019-07-27 rev.B initial release
2019-07-27 ERRATA
2019-07-29 added DivMMC edition
2019-07-29 some cleanup and refactoring
2019-07-30 small refactoring
2019-07-31 Updated ERRATA
2019-08-17 revC, initial revision
2019-08-18 final revision rev.C
2019-08-18 latest schematics
2019-08-18 gerbers revC
2019-08-18 added gitignore, updated revC docs
2019-08-18 updated cdf
2019-08-18 Updated gitignore
2019-09-10 Delete karabas-nano-gerbers-revC.zip
    Broken PLCC32 footprint
2019-09-10 Fixed PLCC32 footprint
2019-10-08 revC firmware (divmmc version)
2019-10-08 added avray firmware
2019-10-08 revC firmware (z-controller)
2019-10-11 Updated revC docs
2019-10-15 Removed M1 signal from the AY port decoding
2019-10-20 cleanup, bugfixes
2019-10-21 Added AVR AY emul binaries
2019-10-21 removed m168 firmware
2019-10-23 Pentagon 512 (via 7ffd) + divmmc 512
2019-10-24 1024 ram via #DFFD
2019-10-24 fixed 7ffd port decoding
2019-10-26 pcb rev.D
2019-10-26 added rev.D renders
2019-10-26 revD docs
2020-01-19 latest fixes
2020-01-19 revD photo
2020-01-19 Universal (configurable) firmware for EPM7512 with DivMMC, UART, Timex video modes
2020-01-19 reorganized cpld sources and releases
2020-01-19 added src gitignore to filter pof binaries
2020-04-09 Changed video DAC output a bit
2020-04-09 new release for EPM3256 with UART on AY port A
2020-04-09 Renamed a firmware for EPM7512
2020-04-09 Z-Controller release with UART on AY port A for EPM3256
2020-04-09 Reorganized old firmware sources
2020-04-12 wifi addon PCB rev.A for karabas-nano
2020-04-12 wifi module renders
2020-04-12 Rev.E pcb with ESP-12 module
2020-04-12 updated sd card contents for the rev.E with Wi-Fi module
2020-05-25 Added gerbers rev.F
2020-05-25 latest changes
2020-05-25 rev.F - initial revision
2020-05-25 Rev.F docs
2020-05-25 removed rev.E
2020-06-01 New PCB rev.G
2020-06-01 Added project files for HW revision rev.G
2020-06-04 reverted rev.E materials
2020-06-28 Removed unused ZX UNO UART and timex modes
2020-06-28 fixed out of sync between schematics and pcb
2020-06-28 release 1.2
2020-06-28 removed zx uno uart code
2020-06-30 more cleanup and refactoring: added IP core megafunction for shift registers
2020-06-30 updated release 1.2
2020-07-08 refactoring
2020-07-08 combined video controller
2020-07-11 added rgbi to 9 bit component
2021-02-28 revH. initial version
2021-03-01 Added 3.3/5v selectors for memory and generator
2021-03-01 small improvements
2021-03-01 updated revCmmc
2021-03-03 Rev.H
2021-03-20 divmmc rom with esxdos 0.8.8
2021-03-20 updated esxdos 0.8.8
2021-04-29 added .gitattributes
2021-04-29 added pcb rev.I (work in progress)
2021-04-29 updated .gitignore for kicad 6
2021-07-08 upload final pcb rev.I files
2021-07-08 add avr turbosound firmware for rev.I
2021-07-08 rev.I (#2)
    * added .gitattributes
    * updated .gitignore for kicad 6
    * added pcb rev.I (work in progress)
    * upload final pcb rev.I files
    * add avr turbosound firmware for rev.I
2021-07-08 update rev.I gerbers
2021-07-08 update rev.I gerbers (#3)
2021-07-09 Updated 3d models on revI board
2021-07-10 Small improvements: moved RN3 outside the plcc32 socket, rerouted vias under logo
2021-07-26 Changed label due to PCBWay violations
2021-11-15 Added pcb rev.J
2021-11-15 Added revJ schematics
2021-11-15 revJ gerbers
2022-06-02 latest working tree changes
2022-06-02 Added flags to build the firmware with different clock sources
2022-06-02 some uncommited roms and software
2022-06-02 Refactored roms
2022-06-03 updated esxdos to 0.8.9
2022-07-30 Added datasheets for used electronic components
2022-07-31 Added datasheets for used electronic components (#5)
2022-08-05 Added a photos of the assembled PCB Rev. H by Xoomoh
2022-08-09 Added more options to generate bitstream
